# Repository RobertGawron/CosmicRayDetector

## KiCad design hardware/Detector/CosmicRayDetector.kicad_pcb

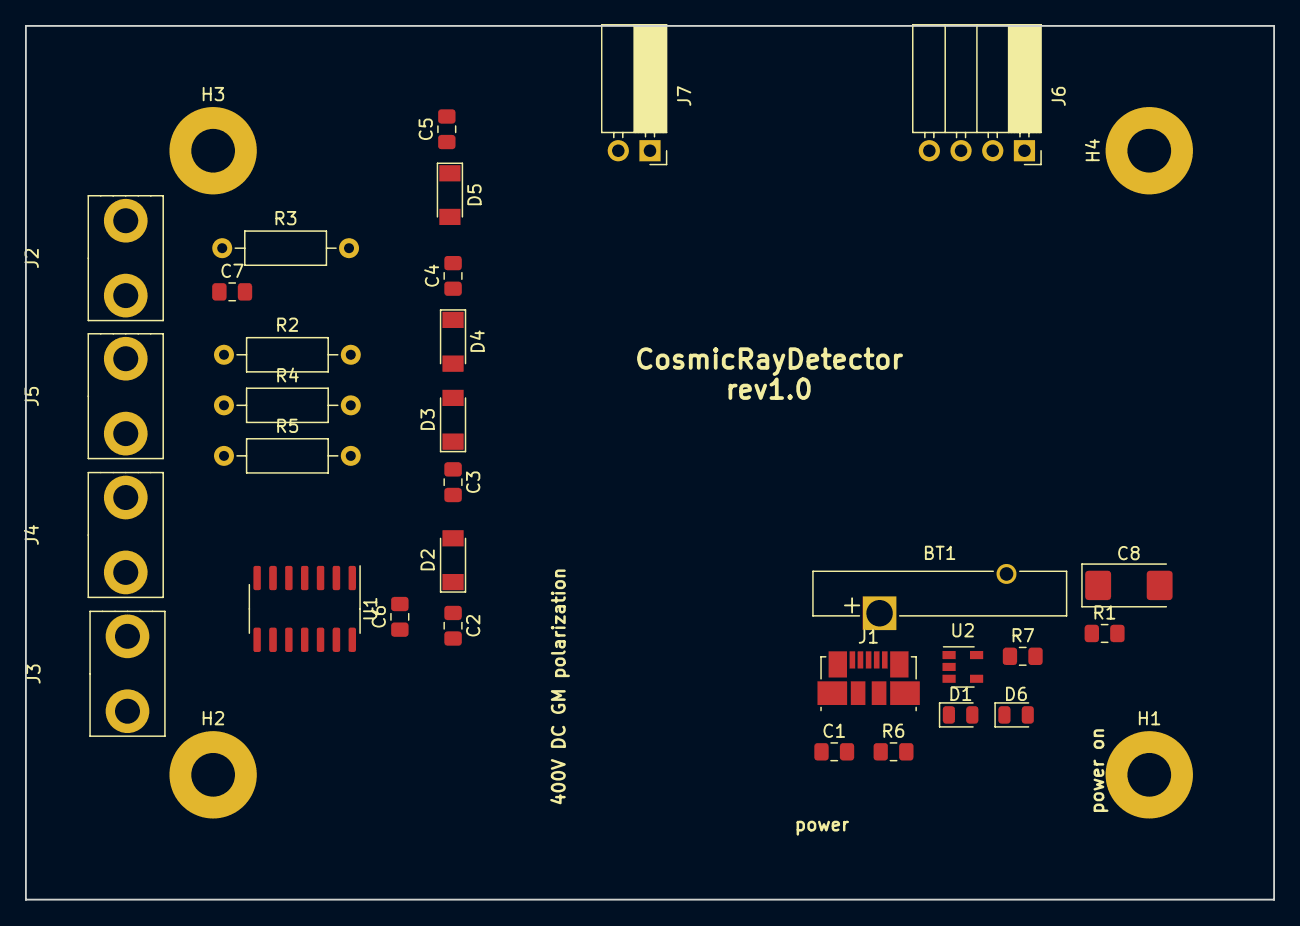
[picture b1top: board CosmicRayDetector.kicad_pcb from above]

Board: 2 copper layers, 100.0 x 70.0 mm, 35 parts (0 on the bottom side), 15 nets, no tracks yet.

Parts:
BT1: Battery_Cell; Battery_Panasonic_CR2025-V1AK_Vertical_CircularHoles
C1, C7: 100n; C_0805_2012Metric_Pad1.15x1.40mm_HandSolder
C2, C3, C4, C5, C6: C; C_0805_2012Metric_Pad1.15x1.40mm_HandSolder
C8: 10u; CP_EIA-6032-28_Kemet-C
D1, D6: red; LED_0805_2012Metric
D2, D3, D4, D5: D_Zener; D_MiniMELF
H1, H2, H3, H4: MountingHole_Pad; MountingHole_3.5mm_Pad
J1: USB_B_Micro; USB_Micro-B_Molex_47346-0001
J2, J3, J4, J5: Conn_01x01_Female; GeigerTube
J6: Conn_01x04; PinSocket_1x04_P2.54mm_Horizontal
J7: Conn_01x02; PinSocket_1x02_P2.54mm_Horizontal
R1: 520R; R_0805_2012Metric_Pad1.15x1.40mm_HandSolder
R2, R3, R4, R5: R; R_Axial_DIN0207_L6.3mm_D2.5mm_P10.16mm_Horizontal
R6: 2k2; R_0805_2012Metric_Pad1.15x1.40mm_HandSolder
R7: 470R; R_0805_2012Metric_Pad1.15x1.40mm_HandSolder
U1: HEF4093B; SOIC-14_3.9x8.7mm_P1.27mm
U2: MCP73831-5-OT; SOT-23-5

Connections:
GM1: J6.1, U1.10
GM2: J6.2, U1.11
GM3: J6.3, U1.3
GM4: J6.4, U1.4
GND: BT1.2, C1.1, C2.2, C3.2, C4.2, C5.2, C6.2, C7.2, C8.2, D2.2, D3.2, D4.2, D5.2, H1.1, H2.1, H3.1, H4.1, J1.5, J1.6, J7.2, R1.2, R2.2, R3.2, R4.2, R5.2, R6.2, U1.7, U2.2
unnamed: BT1.1, C8.1, U2.3
unnamed: C2.1, D2.1, J2.1, R2.1, U1.8, U1.9
unnamed: C3.1, D3.1, J3.1, R3.1, U1.12, U1.13
unnamed: C4.1, D4.1, J4.1, R4.1, U1.1, U1.2
unnamed: C5.1, D5.1, J5.1, R5.1, U1.5, U1.6
unnamed: D1.1, R1.1
unnamed: D6.1, R7.1
unnamed: R6.1, U2.5
unnamed: R7.2, U2.1
VCC_5V: C1.2, C6.1, C7.1, D1.2, D6.2, J1.1, J7.1, U1.14, U2.4

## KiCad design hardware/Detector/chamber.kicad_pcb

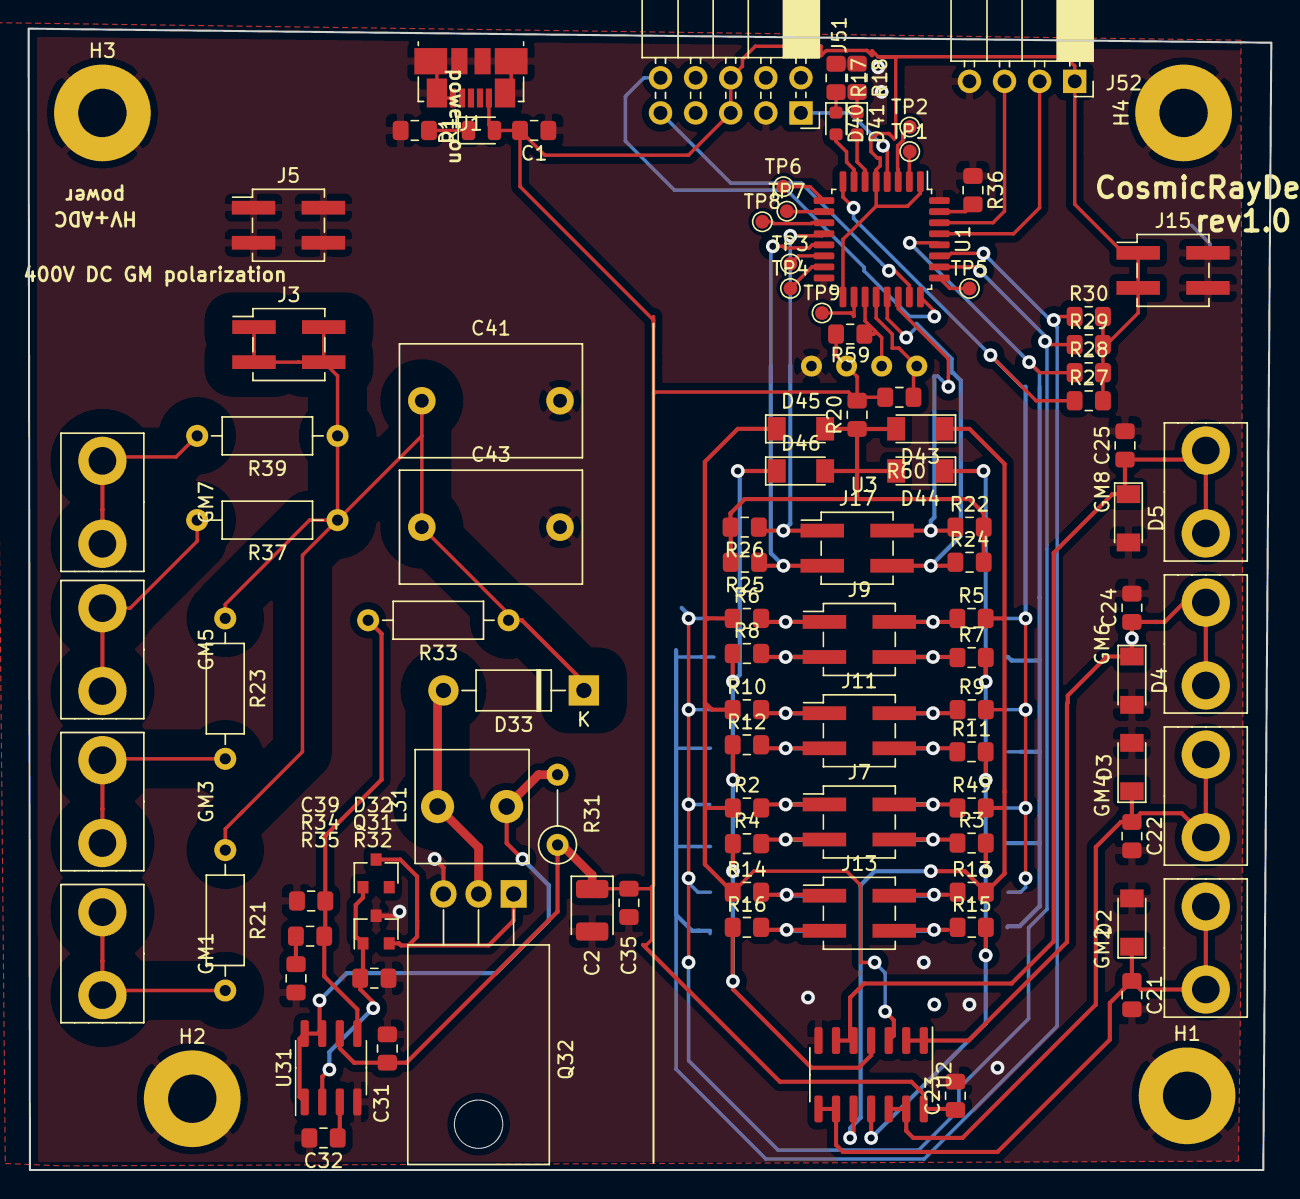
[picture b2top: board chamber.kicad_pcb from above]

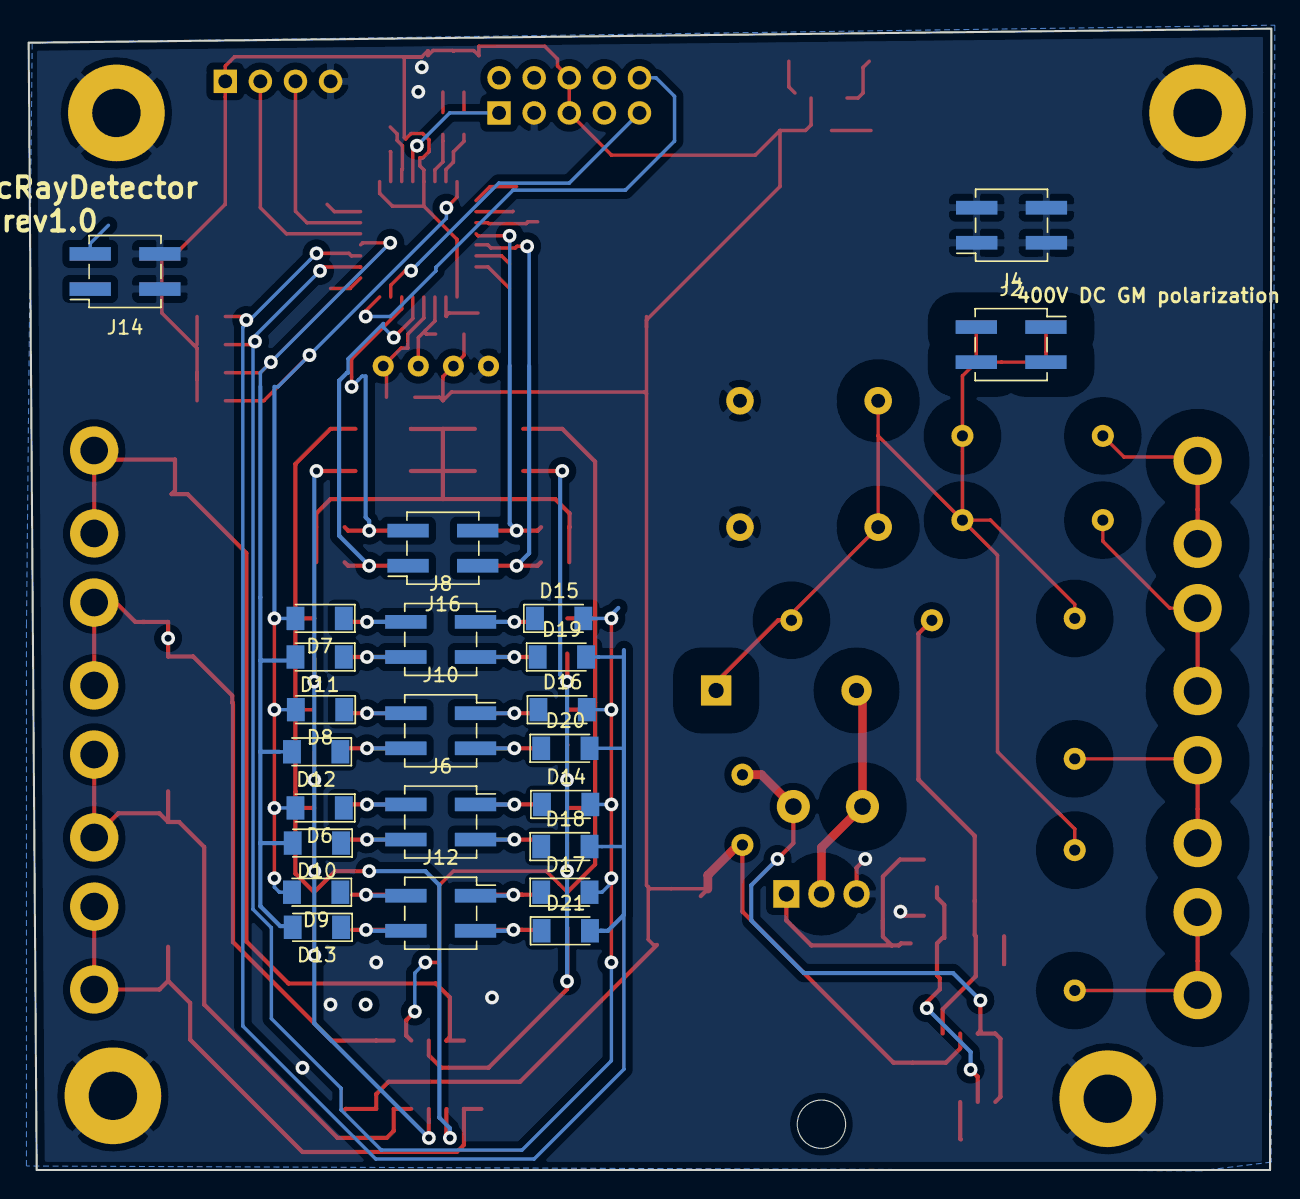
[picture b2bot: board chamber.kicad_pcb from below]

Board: 2 copper layers, 89.9 x 82.6 mm, 129 parts (24 on the bottom side), 69 nets.

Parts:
C1, C31, C35: 100n; C_0805_2012Metric_Pad1.15x1.40mm_HandSolder
C2: 100u/6V3; CP_EIA-3528-21_Kemet-B
C21, C22, C23, C24, C25: C; C_0805_2012Metric_Pad1.15x1.40mm_HandSolder
C32: 3n2; C_0805_2012Metric_Pad1.15x1.40mm_HandSolder
C39: 10n; C_0805_2012Metric_Pad1.15x1.40mm_HandSolder
C41, C43: 10n/600V; C_Rect_L13.0mm_W8.0mm_P10.00mm_FKS3_FKP3_MKS4
D1: red; LED_0805_2012Metric
D2, D3, D4, D5: D_Zener; D_MiniMELF
D6, D7, D8, D9, D10, D11, D12, D13, D14, D15, D16, D17, D18, D19, D20, D21, D43, D44, D45, D46: 1n148; D_MiniMELF
D32: D_Schottky; D_SOT-23_ANK
D33: 1N4007; D_DO-41_SOD81_P10.16mm_Horizontal
D40, D41: LED; LED_0603_1608Metric
GM1, GM3, GM5, GM7: GM+; GeigerTube
GM2, GM4, GM6, GM8: GM-; GeigerTube
H1, H2, H3, H4: MountingHole_Pad; MountingHole_3.5mm_Pad
J1: USB_B_Micro; USB_Micro-B_Molex_47346-0001
J2, J4, J6, J8, J10, J12, J14, J16: Conn_02x02_Odd_Even; PinSocket_2x02_P2.54mm_Vertical_SMD
J3, J5, J7, J9, J11, J13, J15, J17: Conn_02x02_Odd_Even; PinHeader_2x02_P2.54mm_Vertical_SMD
J51: Conn_02x05_Counter_Clockwise; PinSocket_2x05_P2.54mm_Horizontal
J52: Conn_01x04; PinSocket_1x04_P2.54mm_Horizontal
L31: 680m; L_Radial_L8.0mm_W8.0mm_P5.00mm_Neosid_NE-CPB-07E
Q31: BC859; SOT-23
Q32: Q_NMOS_GDS; TO-220-3_Horizontal_TabDown
R1: 520R; R_0805_2012Metric_Pad1.15x1.40mm_HandSolder
R2, R3, R4, R5, R6, R7, R8, R9, R10, R11, R12, R13, R14, R15, R16, R20, R22, R24, R25, R26, R49: R; R_0805_2012Metric_Pad1.15x1.40mm_HandSolder
R17, R18, R27, R28, R29, R30: 680R; R_0805_2012Metric_Pad1.15x1.40mm_HandSolder
R21, R23, R37, R39: R; R_Axial_DIN0207_L6.3mm_D2.5mm_P10.16mm_Horizontal
R31: R22/0.5W; R_Axial_DIN0207_L6.3mm_D2.5mm_P5.08mm_Vertical
R32: 10k; R_0805_2012Metric_Pad1.15x1.40mm_HandSolder
R33: 10M; R_Axial_DIN0207_L6.3mm_D2.5mm_P10.16mm_Horizontal
R34: 1k; R_0805_2012Metric_Pad1.15x1.40mm_HandSolder
R35: 30k; R_0805_2012Metric_Pad1.15x1.40mm_HandSolder
R36: 100k; R_0805_2012Metric_Pad1.15x1.40mm_HandSolder
R59, R60: 2k2; R_0805_2012Metric_Pad1.15x1.40mm_HandSolder
TP1, TP2, TP3, TP4, TP5, TP6, TP7, TP8, TP9: TestPoint; TestPoint_Pad_D1.0mm
U1: STM32F030K6Tx; LQFP-32_7x7mm_P0.8mm
U2: HEF4093B; SOIC-14_3.9x8.7mm_P1.27mm
U3: LCD_I2C
U31: MC34063AD; SOIC-8_3.9x4.9mm_P1.27mm

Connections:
/DataAcquisition/NRST: J51.1, U1.4
/DataAcquisition/RX: J52.3, U1.30
/DataAcquisition/SWCLK: J51.10, U1.24
/DataAcquisition/SWDIO: J51.9, U1.23
/DataAcquisition/TX: J52.2, U1.29
COL0: D6.2, D7.2, D8.2, D9.2, R27.1, U1.8
COL1: D10.2, D11.2, D12.2, D13.2, R28.1, U1.28
COL2: D14.2, D15.2, D16.2, D17.2, R29.1, U1.26
COL3: D18.2, D19.2, D20.2, D21.2, R30.1, U1.27
GM1: D43.1, R5.2, R9.2, R13.2, R49.2, U2.10
GM2: D44.1, R3.2, R7.2, R11.2, R15.2, U2.11
GM3: D45.1, R2.1, R6.1, R10.1, R14.1, U2.3
GM4: D46.1, R4.1, R8.1, R12.1, R16.1, U2.4
GM_LAMP_POLARIZATION: C41.1, C43.1, D33.1, J2.1, J2.2, J2.3, J2.4, J3.1, J3.2, J3.3, J3.4, R21.1, R23.1, R33.1, R37.1, R39.1
GND: C1.1, C2.2, C21.2, C22.2, C23.2, C24.2, C25.2, C31.1, C32.2, C35.2, C39.2, C41.2, C43.2, D2.2, D3.2, D4.2, D5.2, H1.1, H2.1, H3.1, H4.1, J1.5, J1.6, J4.1, J4.2, J4.3, J4.4, J5.1, J5.2, J5.3, J5.4, J14.2, J14.4, J15.2, J15.4, J51.3, J52.4, Q31.3, Q32.3, R1.2, R17.1, R18.1, R32.2, R35.2, R36.1, U1.16, U1.32, U2.7, U3.4, U31.4
INT01: D6.1, J6.2, J7.2, R49.1
INT02: D10.1, J6.4, J7.4, R3.1
INT03: D14.1, J6.1, J7.1, R2.2
INT04: D18.1, J6.3, J7.3, R4.2
INT11: D7.1, J8.2, J9.2, R5.1
INT12: D11.1, J8.4, J9.4, R7.1
INT13: D15.1, J8.1, J9.1, R6.2
INT14: D19.1, J8.3, J9.3, R8.2
INT21: D8.1, J10.2, J11.2, R9.1
INT22: D12.1, J10.4, J11.4, R11.1
INT23: D16.1, J10.1, J11.1, R10.2
INT24: D20.1, J10.3, J11.3, R12.2
INT31: D9.1, J12.2, J13.2, R13.1
INT32: D13.1, J12.4, J13.4, R15.1
INT33: D17.1, J12.1, J13.1, R14.2
INT34: D21.1, J12.3, J13.3, R16.2
unnamed: C21.1, D2.1, GM2.1, U2.8, U2.9
unnamed: C22.1, D3.1, GM4.1, U2.12, U2.13
unnamed: C24.1, D4.1, GM6.1, U2.1, U2.2
unnamed: C25.1, D5.1, GM8.1, U2.5, U2.6
unnamed: C32.1, U31.3
unnamed: C39.1, R33.2, R34.1, U31.5
unnamed: D1.1, R1.1
unnamed: D32.1, Q31.2, Q32.1
unnamed: D32.2, Q31.1, R32.1, U31.2
unnamed: D33.2, L31.2, Q32.2
unnamed: D40.1, R17.2
unnamed: D40.2, U1.7
unnamed: D41.1, R18.2
unnamed: D41.2, U1.6
unnamed: D43.2, D44.2, D45.2, D46.2, R20.1, R22.2, R24.2, R25.2, R26.2
unnamed: GM1.1, R21.2
unnamed: GM3.1, R23.2
unnamed: GM5.1, R37.2
unnamed: GM7.1, R39.2
unnamed: L31.1, R31.2, U31.1, U31.7, U31.8
unnamed: R34.2, R35.1
unnamed: R36.2, U1.31
unnamed: R59.1, U1.19, U3.2
unnamed: R60.1, U1.20, U3.1
unnamed: TP1.1, U1.2
unnamed: TP2.1, U1.3
unnamed: TP3.1, U1.14
unnamed: TP4.1, U1.15
unnamed: TP5.1, U1.25
unnamed: TP6.1, U1.9
unnamed: TP7.1, U1.10
unnamed: TP8.1, U1.11
unnamed: TP9.1, U1.18
ROW0: J16.2, J17.2, R22.1, U1.22
ROW1: J16.4, J17.4, R24.1, U1.21
ROW2: J16.3, J17.3, R25.1, U1.13
ROW3: J16.1, J17.1, R26.1, U1.12
VCC_5V: C1.2, C2.1, C23.1, C31.2, C35.1, D1.2, J1.1, J14.1, J14.3, J15.1, J15.3, J51.5, J51.6, J52.1, R20.2, R27.2, R28.2, R29.2, R30.2, R31.1, R59.2, R60.2, U1.1, U1.5, U1.17, U2.14, U3.3, U31.6

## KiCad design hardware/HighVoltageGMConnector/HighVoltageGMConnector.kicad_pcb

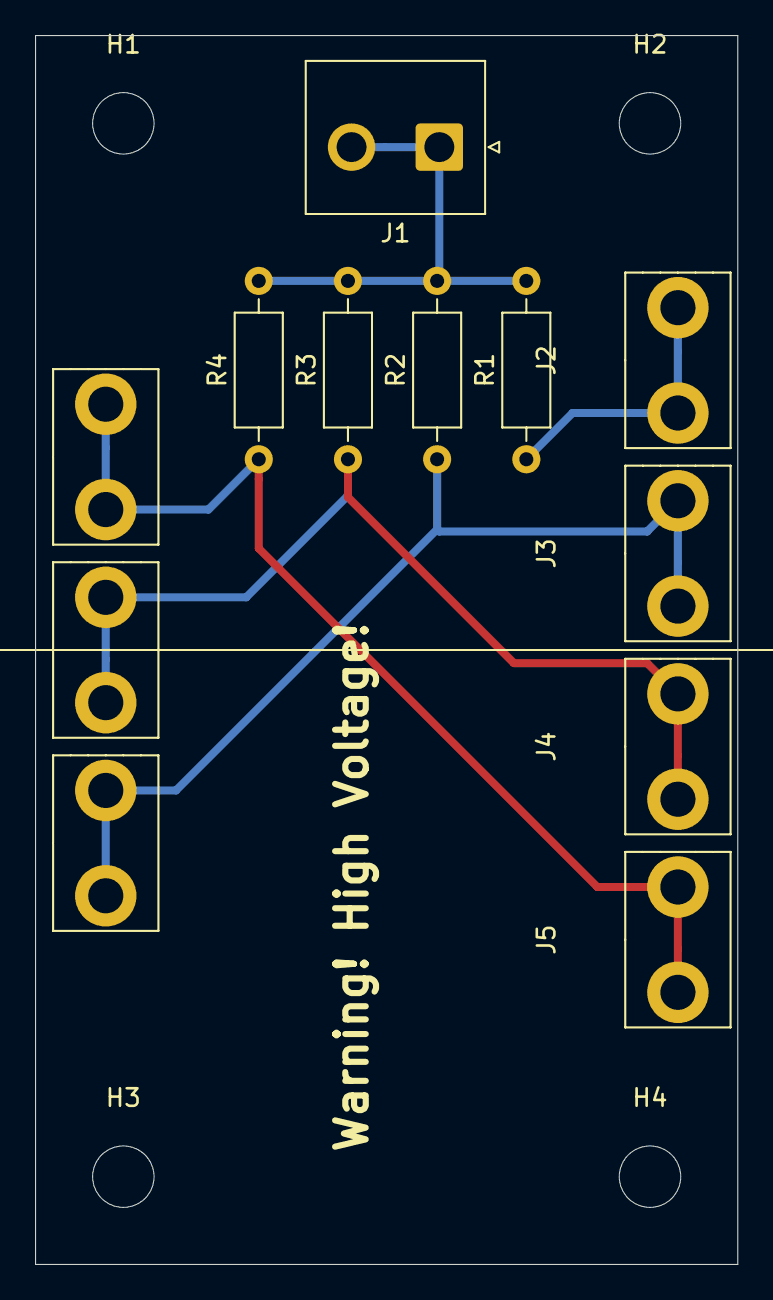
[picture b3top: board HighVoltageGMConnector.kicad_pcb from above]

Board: 2 copper layers, 40.0 x 70.0 mm, 16 parts (0 on the bottom side), 5 nets.

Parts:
H1, H2, H3, H4: MountingHole; MountingHole_3.5mm
J1: Conn_01x02_Male; JST_NV_B02P-NV_1x02_P5.00mm_Vertical
J2, J3, J4, J5, J6, J7, J8: Conn_01x01_Female; GeigerTube
R1, R2, R3, R4: 6M8; R_Axial_DIN0207_L6.3mm_D2.5mm_P10.16mm_Horizontal

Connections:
unnamed: J1.1, J1.2, R1.2, R2.2, R3.2, R4.2
unnamed: J2.1, R1.1
unnamed: J3.1, J6.1, R2.1
unnamed: J4.1, J7.1, R3.1
unnamed: J5.1, J8.1, R4.1
